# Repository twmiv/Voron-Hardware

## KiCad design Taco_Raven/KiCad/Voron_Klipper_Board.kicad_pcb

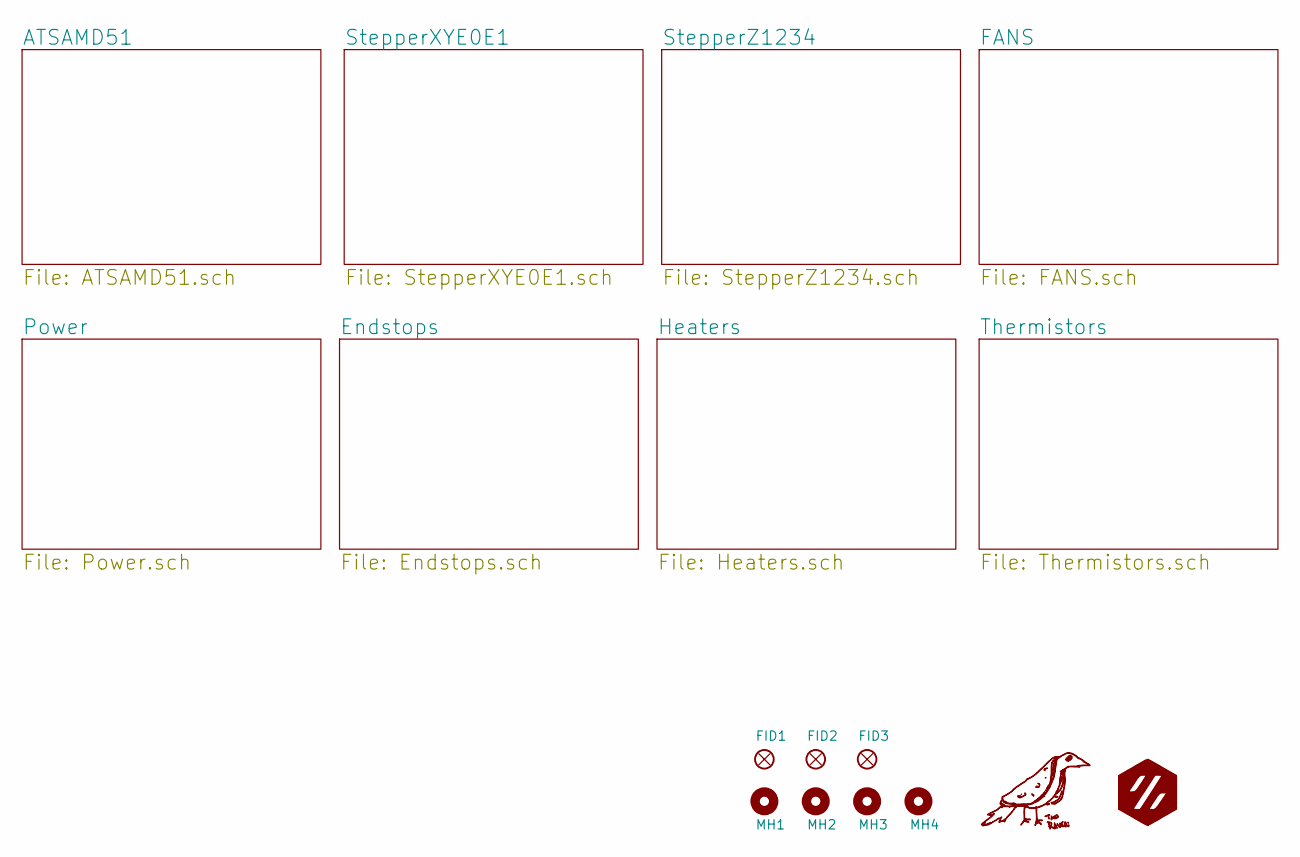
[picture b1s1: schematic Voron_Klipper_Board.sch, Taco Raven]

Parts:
FID1, FID2, FID3: FIDUCIAL_1MM; Fiducial_1mm_Dia_2.54mm_Outer_CopperBottom
G1: TACo; taco
G2: mzbot; LOGO
MH1, MH2, MH3, MH4: MountingHole; MountingHole_3.2mm_M3_DIN965

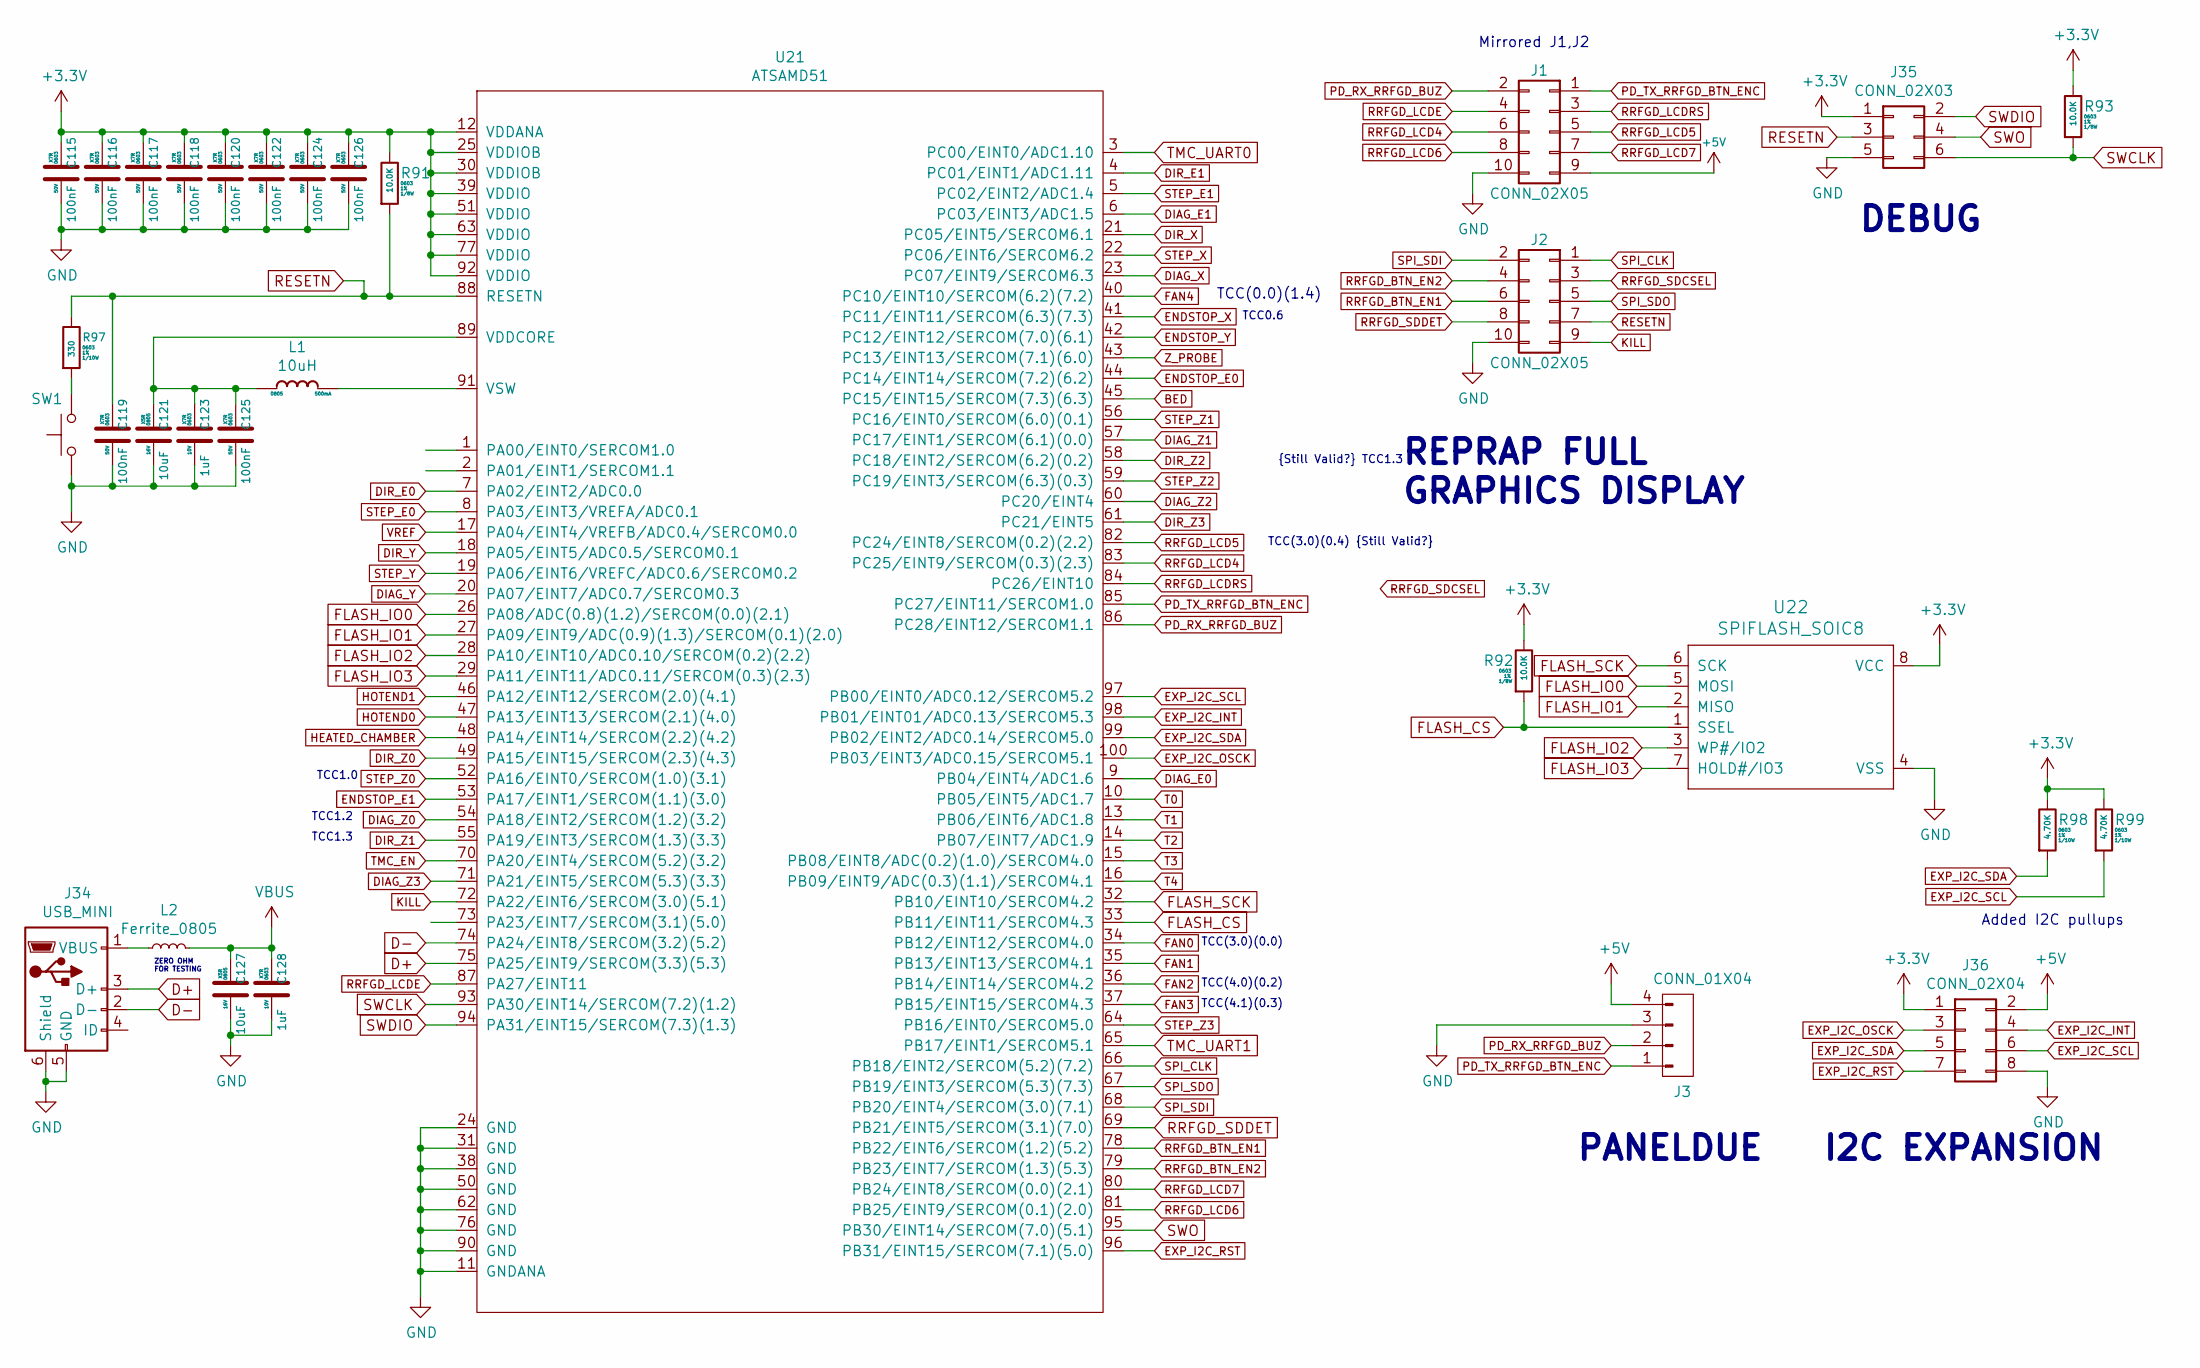
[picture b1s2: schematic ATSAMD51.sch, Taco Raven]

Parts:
C115, C116, C117, C118, C119, C120, C122, C124, C125, C126: 100nF; C_0603; Voltage 50V; MFG PN CC0603KRX7R9BB104; Digikey P/N 311-1344-1-ND
C121, C127: 10uF; C_0805; Voltage 16V; MFG PN CL21A106KOQNNWE; Digikey P/N 1276-2894-1-ND
C123, C128: 1uF; C_0603; Voltage 10V; MFG PN CL10B105KP8NNNC; Digikey P/N 1276-1946-1-ND
J1, J2: CONN_02X05; PinSocket_2x05_P2.54mm_Vertical; MFG PN 302-S101; Digikey P/N ED1543-ND
J3: CONN_01X04; Molex_KK_1X4; MFG PN 0022232041; Digikey P/N WM4202-ND
J34: USB_MINI; USB_Mini-B_Lumberg_2486_01_Horizontal; MFG PN 690-005-299-043; Digikey P/N 151-1206-1-ND
J35: CONN_02X03; PinHeader_2x03_P2.54mm_Vertical
J36: CONN_02X04; PinHeader_2x04_P2.54mm_Vertical; MFG PN 75869-332LF; Digikey P/N 609-5123-ND
L1: 10uH; L_0805_2012Metric; MFG PN MLZ2012N100LT000; Digikey P/N 445-6762-1-ND
L2: Ferrite_0805; L_0805_2012Metric; MFG PN CRCW08050000Z0EA; Digikey P/N 541-0.0ACT-ND
R91, R92, R93: 10.0K; R_0603; Tolerance 1%; MFG PN RNCP0603FTD10K0; Digikey P/N RNCP0603FTD10K0CT-ND
R97: 330; R_0603; Tolerance 1%; MFG PN RMCF0603JT330R; Digikey P/N RMCF0603JT330RCT-ND
R98, R99: 4.70K; R_0603; Tolerance 1%; MFG PN RC0603FR-074K7L; Digikey P/N 311-4.70KHRCT-ND
SW1: SW_Push; SW_SPST_B3S-1000; MFG PN B3S-1000P; Digikey P/N SW836CT-ND
U21: ATSAMD51; TQFP-100_14x14mm_P0.5mm; MFG PN ATSAMD51N19A-AU; Digikey P/N ATSAMD51N19A-AU-ND
U22: SPIFLASH_SOIC8; SOIC-8_3.9x4.9mm_Pitch1.27mm; MFG PN AT25SF041-SSHD-T; Digikey P/N 1265-1131-1-ND

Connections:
+3.3V: C115.2, C116.2, C117.2, C118.2, C120.2, C122.2, C124.2, C126.2, J35.1, J36.1, R91.1, R92.1, R93.1, R98.1, R99.1, U21.12 (VDDANA), U21.25 (VDDIOB), U21.30 (VDDIOB), U21.39 (VDDIO), U21.51 (VDDIO), U21.63 (VDDIO), U21.77 (VDDIO), U21.92 (VDDIO), U22.8 (VCC); also elsewhere on the board
+5V: J1.9, J3.4, J36.2; also elsewhere on the board
BED: U21.45 (PC15/EINT15/SERCOM(7.3)(6.3)); also elsewhere on the board
D+: J34.3 (D+), U21.75 (PA25/EINT9/SERCOM(3.3)(5.3))
D-: J34.2 (D-), U21.74 (PA24/EINT8/SERCOM(3.2)(5.2))
DIAG_E0: U21.9 (PB04/EINT4/ADC1.6); also elsewhere on the board
DIAG_E1: U21.6 (PC03/EINT3/ADC1.5); also elsewhere on the board
DIAG_X: U21.23 (PC07/EINT9/SERCOM6.3); also elsewhere on the board
DIAG_Y: U21.20 (PA07/EINT7/ADC0.7/SERCOM0.3); also elsewhere on the board
DIAG_Z0: U21.54 (PA18/EINT2/SERCOM(1.2)(3.2)); also elsewhere on the board
DIAG_Z1: U21.57 (PC17/EINT1/SERCOM(6.1)(0.0)); also elsewhere on the board
DIAG_Z2: U21.60 (PC20/EINT4); also elsewhere on the board
DIAG_Z3: U21.71 (PA21/EINT5/SERCOM(5.3)(3.3)); also elsewhere on the board
DIR_E0: U21.7 (PA02/EINT2/ADC0.0); also elsewhere on the board
DIR_E1: U21.4 (PC01/EINT1/ADC1.11); also elsewhere on the board
DIR_X: U21.21 (PC05/EINT5/SERCOM6.1); also elsewhere on the board
DIR_Y: U21.18 (PA05/EINT5/ADC0.5/SERCOM0.1); also elsewhere on the board
DIR_Z0: U21.49 (PA15/EINT15/SERCOM(2.3)(4.3)); also elsewhere on the board
DIR_Z1: U21.55 (PA19/EINT3/SERCOM(1.3)(3.3)); also elsewhere on the board
DIR_Z2: U21.58 (PC18/EINT2/SERCOM(6.2)(0.2)); also elsewhere on the board
DIR_Z3: U21.61 (PC21/EINT5); also elsewhere on the board
ENDSTOP_E0: U21.44 (PC14/EINT14/SERCOM(7.2)(6.2)); also elsewhere on the board
ENDSTOP_E1: U21.53 (PA17/EINT1/SERCOM(1.1)(3.0)); also elsewhere on the board
ENDSTOP_X: U21.41 (PC11/EINT11/SERCOM(6.3)(7.3)); also elsewhere on the board
ENDSTOP_Y: U21.42 (PC12/EINT12/SERCOM(7.0)(6.1)); also elsewhere on the board
EXP_I2C_INT: J36.4, U21.98 (PB01/EINT01/ADC0.13/SERCOM5.3)
EXP_I2C_OSCK: J36.3, U21.100 (PB03/EINT3/ADC0.15/SERCOM5.1)
EXP_I2C_RST: J36.7, U21.96 (PB31/EINT15/SERCOM(7.1)(5.0))
EXP_I2C_SCL: J36.6, R99.2, U21.97 (PB00/EINT0/ADC0.12/SERCOM5.2)
EXP_I2C_SDA: J36.5, R98.2, U21.99 (PB02/EINT2/ADC0.14/SERCOM5.0)
FAN0: U21.34 (PB12/EINT12/SERCOM4.0); also elsewhere on the board
FAN1: U21.35 (PB13/EINT13/SERCOM4.1); also elsewhere on the board
FAN2: U21.36 (PB14/EINT14/SERCOM4.2); also elsewhere on the board
FAN3: U21.37 (PB15/EINT15/SERCOM4.3); also elsewhere on the board
FAN4: U21.40 (PC10/EINT10/SERCOM(6.2)(7.2)); also elsewhere on the board
FLASH_CS: R92.2, U21.33 (PB11/EINT11/SERCOM4.3), U22.1 (SSEL)
FLASH_IO0: U21.26 (PA08/ADC(0.8)(1.2)/SERCOM(0.0)(2.1)), U22.5 (MOSI)
FLASH_IO1: U21.27 (PA09/EINT9/ADC(0.9)(1.3)/SERCOM(0.1)(2.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), U22.2 (MISO)
FLASH_IO2: U21.28 (PA10/EINT10/ADC0.10/SERCOM(0.2)(2.2)), U22.3 (WP#/IO2)
FLASH_IO3: U21.29 (PA11/EINT11/ADC0.11/SERCOM(0.3)(2.3)), U22.7 (HOLD#/IO3)
FLASH_SCK: U21.32 (PB10/EINT10/SERCOM4.2), U22.6 (SCK)
GND: C115.1, C116.1, C117.1, C118.1, C119.1, C120.1, C121.1, C122.1, C123.1, C124.1, C125.1, C126.1, C127.1, C128.1, J1.10, J2.10, J3.3, J34.5 (GND), J34.6 (Shield), J35.5, J36.8, SW1.1, U21.11 (GNDANA), U21.24 (GND), U21.31 (GND), U21.38 (GND), U21.50 (GND), U21.62 (GND), U21.76 (GND), U21.90 (GND), U22.4 (VSS); also elsewhere on the board
HEATED_CHAMBER: U21.48 (PA14/EINT14/SERCOM(2.2)(4.2)); also elsewhere on the board
HOTEND0: U21.47 (PA13/EINT13/SERCOM(2.1)(4.0)); also elsewhere on the board
HOTEND1: U21.46 (PA12/EINT12/SERCOM(2.0)(4.1)); also elsewhere on the board
KILL: J2.9, U21.72 (PA22/EINT6/SERCOM(3.0)(5.1))
unnamed: C121.2, C123.2, C125.2, L1.1, U21.89 (VDDCORE)
unnamed: J34.1 (VBUS), L2.1
unnamed: L1.2, U21.91 (VSW)
unnamed: R97.2, SW1.2
PD_RX_RRFGD_BUZ: J1.2, J3.2, U21.86 (PC28/EINT12/SERCOM1.1)
PD_TX_RRFGD_BTN_ENC: J1.1, J3.1, U21.85 (PC27/EINT11/SERCOM1.0)
RESETN: C119.2, J2.7, J35.3, R91.2, R97.1, U21.88 (RESETN)
RRFGD_BTN_EN1: J2.6, U21.78 (PB22/EINT6/SERCOM(1.2)(5.2))
RRFGD_BTN_EN2: J2.4, U21.79 (PB23/EINT7/SERCOM(1.3)(5.3))
RRFGD_LCD4: J1.6, U21.83 (PC25/EINT9/SERCOM(0.3)(2.3))
RRFGD_LCD5: J1.5, U21.82 (PC24/EINT8/SERCOM(0.2)(2.2))
RRFGD_LCD6: J1.8, U21.81 (PB25/EINT9/SERCOM(0.1)(2.0))
RRFGD_LCD7: J1.7, U21.80 (PB24/EINT8/SERCOM(0.0)(2.1))
RRFGD_LCDE: J1.4, U21.87 (PA27/EINT11)
RRFGD_LCDRS: J1.3, U21.84 (PC26/EINT10)
RRFGD_SDCSEL: J2.3
RRFGD_SDDET: J2.8, U21.69 (PB21/EINT5/SERCOM(3.1)(7.0))
SPI_CLK: J2.1, U21.66 (PB18/EINT2/SERCOM(5.2)(7.2))
SPI_SDI: J2.2, U21.68 (PB20/EINT4/SERCOM(3.0)(7.1))
SPI_SDO: J2.5, U21.67 (PB19/EINT3/SERCOM(5.3)(7.3))
STEP_E0: U21.8 (PA03/EINT3/VREFA/ADC0.1); also elsewhere on the board
STEP_E1: U21.5 (PC02/EINT2/ADC1.4); also elsewhere on the board
STEP_X: U21.22 (PC06/EINT6/SERCOM6.2); also elsewhere on the board
STEP_Y: U21.19 (PA06/EINT6/VREFC/ADC0.6/SERCOM0.2); also elsewhere on the board
STEP_Z0: U21.52 (PA16/EINT0/SERCOM(1.0)(3.1)); also elsewhere on the board
STEP_Z1: U21.56 (PC16/EINT0/SERCOM(6.0)(0.1)); also elsewhere on the board
STEP_Z2: U21.59 (PC19/EINT3/SERCOM(6.3)(0.3)); also elsewhere on the board
STEP_Z3: U21.64 (PB16/EINT0/SERCOM5.0); also elsewhere on the board
SWCLK: J35.6, R93.2, U21.93 (PA30/EINT14/SERCOM(7.2)(1.2))
SWDIO: J35.2, U21.94 (PA31/EINT15/SERCOM(7.3)(1.3))
SWO: J35.4, U21.95 (PB30/EINT14/SERCOM(7.0)(5.1))
T0: U21.10 (PB05/EINT5/ADC1.7); also elsewhere on the board
T1: U21.13 (PB06/EINT6/ADC1.8); also elsewhere on the board
T2: U21.14 (PB07/EINT7/ADC1.9); also elsewhere on the board
T3: U21.15 (PB08/EINT8/ADC(0.2)(1.0)/SERCOM4.0); also elsewhere on the board
T4: U21.16 (PB09/EINT9/ADC(0.3)(1.1)/SERCOM4.1); also elsewhere on the board
TMC_EN: U21.70 (PA20/EINT4/SERCOM(5.2)(3.2)); also elsewhere on the board
TMC_UART0: U21.3 (PC00/EINT0/ADC1.10); also elsewhere on the board
TMC_UART1: U21.65 (PB17/EINT1/SERCOM5.1); also elsewhere on the board
VBUS: C127.2, C128.2, L2.2; also elsewhere on the board
VREF: U21.17 (PA04/EINT4/VREFB/ADC0.4/SERCOM0.0); also elsewhere on the board
Z_PROBE: U21.43 (PC13/EINT13/SERCOM(7.1)(6.0)); also elsewhere on the board

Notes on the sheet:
PANELDUE
REPRAP FULL GRAPHICS DISPLAY
TCC0.6
TCC1.0
TCC1.3
{Still Valid?} TCC1.3
DEBUG
TCC(3.0)(0.0)
TCC(4.0)(0.2)
TCC(4.1)(0.3)
TCC(3.0)(0.4) {Still Valid?}
TCC(0.0)(1.4)
I2C EXPANSION
ZERO OHM FOR TESTING
Mirrored J1,J2
Added I2C pullups
TCC1.2
